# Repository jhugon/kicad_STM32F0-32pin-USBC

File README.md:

# KiCad STM32F0 32-pin with USB

A breakout board for a STM32F0 with 32 pins, connected to a UART-to-USB chip
and USB-C port.

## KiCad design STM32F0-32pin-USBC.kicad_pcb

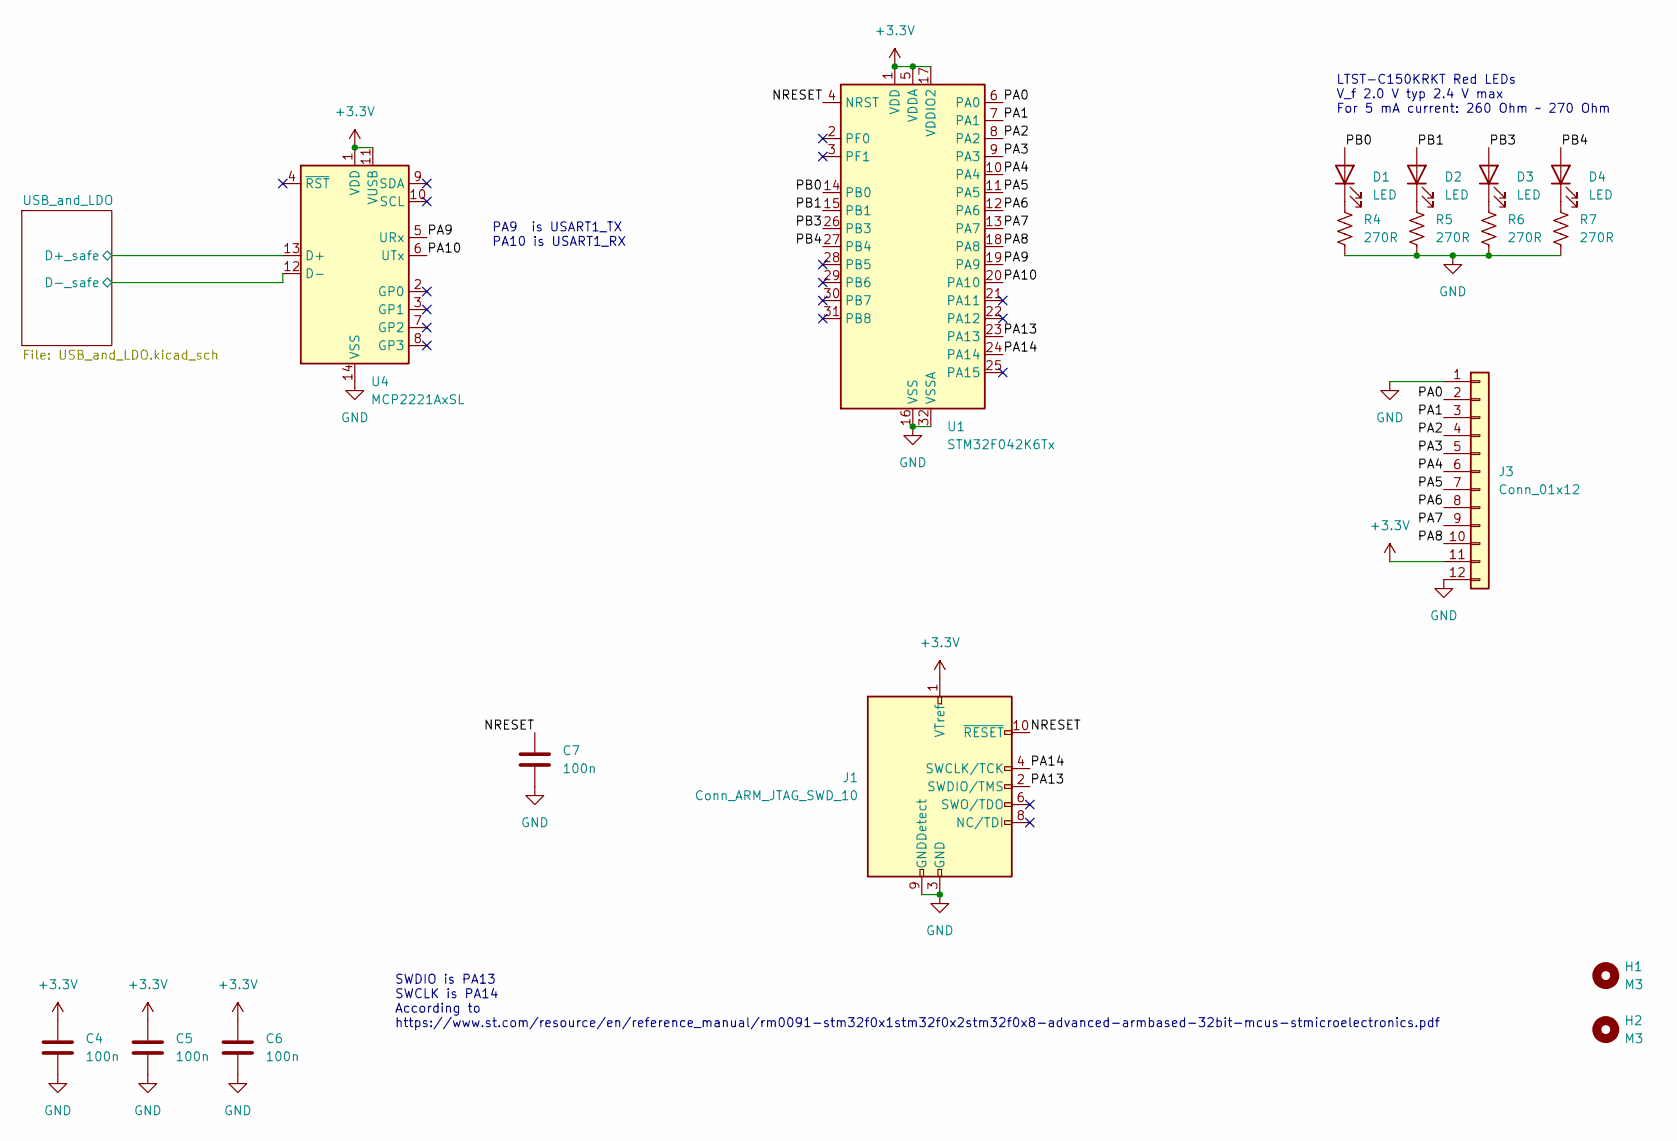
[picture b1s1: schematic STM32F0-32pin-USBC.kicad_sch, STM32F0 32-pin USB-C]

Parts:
C4, C5, C6, C7: 100n; C_0805_2012Metric_Pad1.18x1.45mm_HandSolder; MFR Part No C0805C104K4RACTU
D1, D2, D3, D4: LED; LED_1206_3216Metric_Pad1.42x1.75mm_HandSolder; MFR Part No LTST-C150KRKT
H1, H2: M3; MountingHole_3.2mm_M3
J1: Conn_ARM_JTAG_SWD_10; PinHeader_2x05_P1.27mm_Vertical; MFR Part No FTSH-105-01-L-D-007-K
J3: Conn_01x12; PinHeader_1x12_P2.54mm_Vertical; MFR Part No 9-146285-0
R4, R5, R6, R7: 270R; R_0805_2012Metric_Pad1.20x1.40mm_HandSolder; MFR Part No CRCW0805270RFKEA
U1: STM32F042K6Tx; LQFP-32_7x7mm_P0.8mm; MFR Part No STM32F042K6T6
U4: MCP2221AxSL; SOIC-14_3.9x8.7mm_P1.27mm; MFR Part No MCP2221A-I/SL

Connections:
+3.3V: C4.1, C5.1, C6.1, J1.1 (VTref), J3.11, U1.1 (VDD), U1.5 (VDDA), U1.17 (VDDIO2), U4.1 (VDD), U4.11 (VUSB); also elsewhere on the board
/NRESET: C7.1, J1.10 (~RESET), U1.4 (NRST)
/PA0: J3.2, U1.6 (PA0)
/PA1: J3.3, U1.7 (PA1)
/PA2: J3.4, U1.8 (PA2)
/PA3: J3.5, U1.9 (PA3)
/PA4: J3.6, U1.10 (PA4)
/PA5: J3.7, U1.11 (PA5)
/PA6: J3.8, U1.12 (PA6)
/PA7: J3.9, U1.13 (PA7)
/PA8: J3.10, U1.18 (PA8)
/PA9: U1.19 (PA9), U4.5 (URx)
/PA10: U1.20 (PA10), U4.6 (UTx)
/PA13: J1.2 (SWDIO/TMS), U1.23 (PA13)
/PA14: J1.4 (SWCLK/TCK), U1.24 (PA14)
/PB0: D1.2 (A), U1.14 (PB0)
/PB1: D2.2 (A), U1.15 (PB1)
/PB3: D3.2 (A), U1.26 (PB3)
/PB4: D4.2 (A), U1.27 (PB4)
/USB_and_LDO/D+_safe: U4.13 (D+); also elsewhere on the board
/USB_and_LDO/D-_safe: U4.12 (D-); also elsewhere on the board
GND: C4.2, C5.2, C6.2, C7.2, J1.3 (GND), J1.5 (GND), J1.9 (GNDDetect), J3.1, J3.12, R4.2, R5.2, R6.2, R7.2, U1.16 (VSS), U1.32 (VSSA), U4.14 (VSS); also elsewhere on the board
unnamed: D1.1 (K), R4.1
unnamed: D2.1 (K), R5.1
unnamed: D3.1 (K), R6.1
unnamed: D4.1 (K), R7.1

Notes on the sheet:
SWDIO is PA13 SWCLK is PA14 According to https://www.st.com/resource/en/reference_manual/rm0091-stm32f0x1stm32f0x2stm32f0x8-advanced-armbased-32bit-mcus-stmicroelectronics.pdf
LTST-C150KRKT Red LEDs V_f 2.0 V typ 2.4 V max For 5 mA current: 260 Ohm ~ 270 Ohm
PA9 is USART1_TX PA10 is USART1_RX

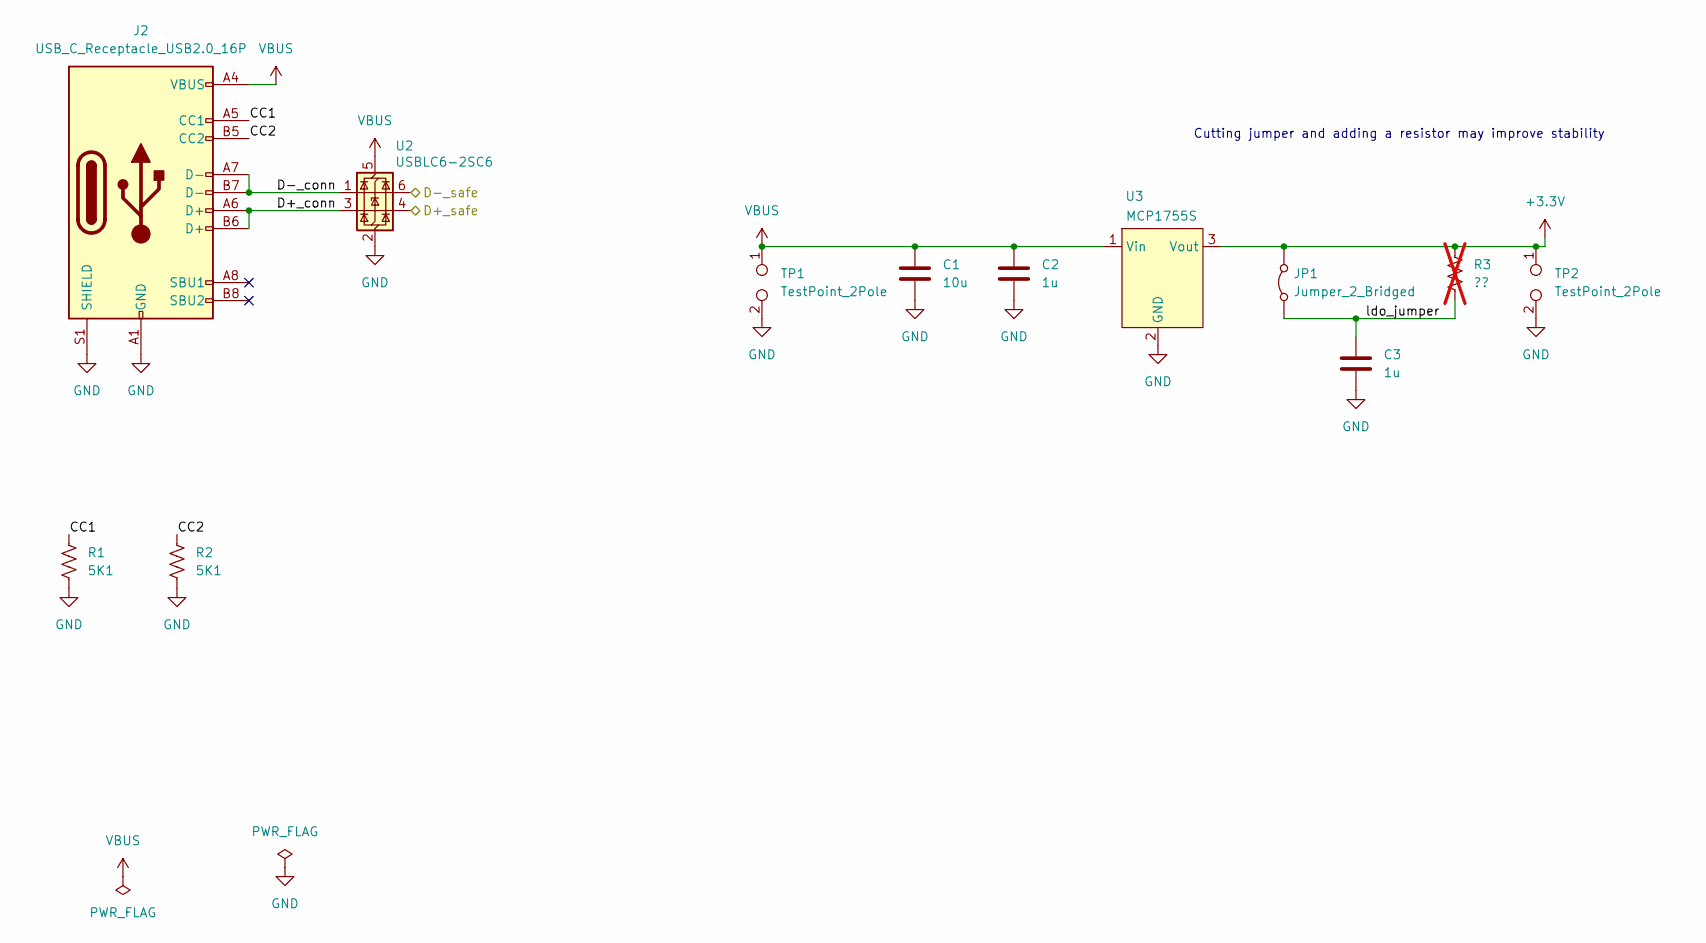
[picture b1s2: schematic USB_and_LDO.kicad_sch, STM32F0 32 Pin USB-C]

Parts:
C1: 10u; C_1206_3216Metric_Pad1.33x1.80mm_HandSolder; MFR Part No C1206C106K4RACTU
C2, C3: 1u; C_0805_2012Metric_Pad1.18x1.45mm_HandSolder; MFR Part No C0805C105K4RACTU
J2: USB_C_Receptacle_USB2.0_16P; USB_C_Receptacle_GCT_USB4085_Reduced_Pad_Size; MFR Part No USB4085-GF-A
JP1: Jumper_2_Bridged; SolderJumper-2_P1.3mm_Bridged_RoundedPad1.0x1.5mm
R1, R2: 5K1; R_0805_2012Metric_Pad1.20x1.40mm_HandSolder; MFR Part No CRCW08055K10FKEA
R3: ??; R_0805_2012Metric_Pad1.20x1.40mm_HandSolder; not fitted
TP1, TP2: TestPoint_2Pole; TestPoint_2Pads_Pitch2.54mm_Drill0.8mm
U2: USBLC6-2SC6; SOT-23-6; MFR Part No USBLC6-2SC6
U3: MCP1755S; SOT-223-3_TabPin2; MFR Part No MCP1755S-XX02E/DB

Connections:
+3.3V: JP1.2 (B), R3.1, TP2.1, U3.3 (Vout); also elsewhere on the board
/USB_and_LDO/CC1: J2.A5 (CC1), R1.1
/USB_and_LDO/CC2: J2.B5 (CC2), R2.1
/USB_and_LDO/D+_conn: J2.A6 (D+), J2.B6 (D+), U2.3 (I/O2)
/USB_and_LDO/D+_safe: U2.4 (I/O2); also elsewhere on the board
/USB_and_LDO/D-_conn: J2.A7 (D-), J2.B7 (D-), U2.1 (I/O1)
/USB_and_LDO/D-_safe: U2.6 (I/O1); also elsewhere on the board
/USB_and_LDO/ldo_jumper: C3.1, JP1.1 (A), R3.2
GND: C1.2, C2.2, C3.2, J2.A1 (GND), J2.A12 (GND), J2.B1 (GND), J2.B12 (GND), J2.S1 (SHIELD), R1.2, R2.2, TP1.2, TP2.2, U2.2 (GND), U3.2 (GND); also elsewhere on the board
VBUS: C1.1, C2.1, J2.A4 (VBUS), J2.A9 (VBUS), J2.B4 (VBUS), J2.B9 (VBUS), TP1.1, U2.5 (VBUS), U3.1 (Vin)

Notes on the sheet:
Cutting jumper and adding a resistor may improve stability

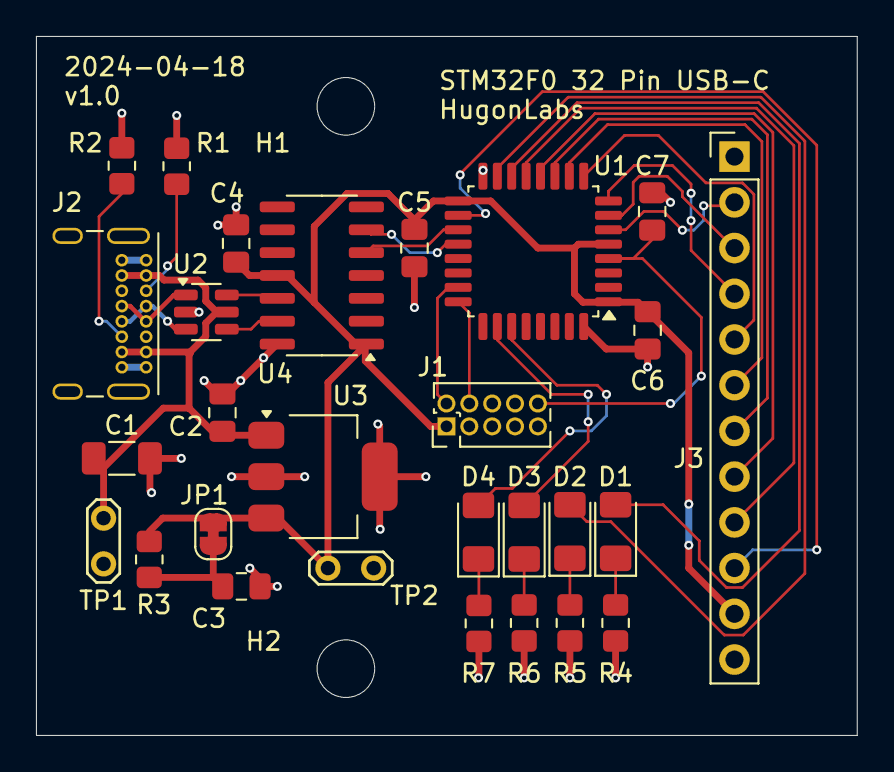
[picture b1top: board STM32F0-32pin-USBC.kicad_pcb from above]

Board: 2 copper layers, 45.6 x 38.8 mm, 30 parts (0 on the bottom side), 32 nets.

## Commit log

2024-04-05 Setup pages and PCB settings for OSHPark
2024-04-05 Added kicad_hugonlib submodule and added libs to project
2024-04-05 Added symbols and completed USB_and_LDO sheet
2024-04-05 work on schematic
2024-04-15 Finished schematic; ERC pass; still need footprints and part nums
2024-04-15 Added all footprints
2024-04-15 finished part nubers in BOM
2024-04-16 preliminary footprint placement
2024-04-16 everything routed but ground
2024-04-16 routing done; many ERC violations
2024-04-16 switched to small pad size usb conn and drew board edge
2024-04-18 update all R's and all C's but 10u to 0805 from 1206
2024-04-18 Changed to 0805 for most Rs and C's
2024-04-18 fixed DRC violations
2024-04-18 Add DRC exclusions
2024-04-18 Added PDFs and renders
2024-04-20 silenced another ERC check
2024-04-22 more DRC exclusions
